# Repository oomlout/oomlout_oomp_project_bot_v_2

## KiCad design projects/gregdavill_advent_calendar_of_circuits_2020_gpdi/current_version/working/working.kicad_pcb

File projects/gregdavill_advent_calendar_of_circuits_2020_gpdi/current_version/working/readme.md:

# advent_calendar_of_circuits_2020
 
## summary 
* id: gregdavill_advent_calendar_of_circuits_2020_gpdi
* user: gregdavill
* name: advent_calendar_of_circuits_2020
* board: gpdi
* repo: https://github.com/gregdavill/advent-calendar-of-circuits-2020
* src_file_repo_kicad_pcb: gpdi/kicad-src/gpdi.kicad_pcb
* src_file_repo_kicad_pcb_link: https://github.com/gregdavill/advent-calendar-of-circuits-2020/tree/main/gpdi/kicad-src/gpdi.kicad_pcb
* src_file_repo_kicad_sch: gpdi/kicad-src/gpdi-sink.kicad_sch
* src_file_repo_kicad_sch_link: https://github.com/gregdavill/advent-calendar-of-circuits-2020/tree/main/gpdi/kicad-src/gpdi-sink.kicad_sch

* src_file_repo_sch: 
* src_file_repo_sch_link: https://github.com/gregdavill/advent-calendar-of-circuits-2020/tree/main/
* full details link: https://github.com/oomlout/oomlout_oomp_project_bot_v_2/tree/main/projects/gregdavill_advent_calendar_of_circuits_2020_gpdi/current_version/working

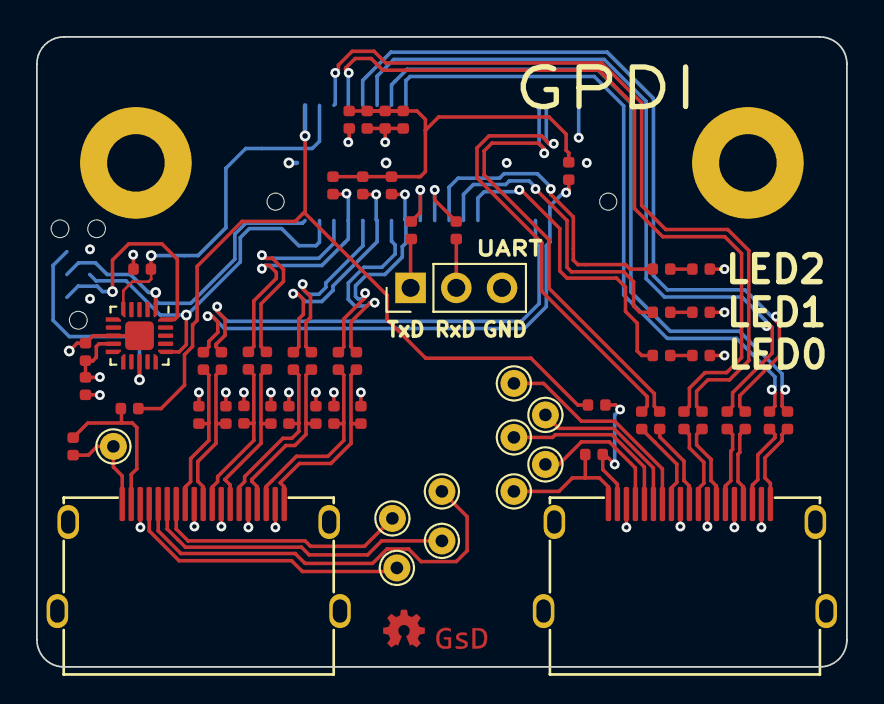
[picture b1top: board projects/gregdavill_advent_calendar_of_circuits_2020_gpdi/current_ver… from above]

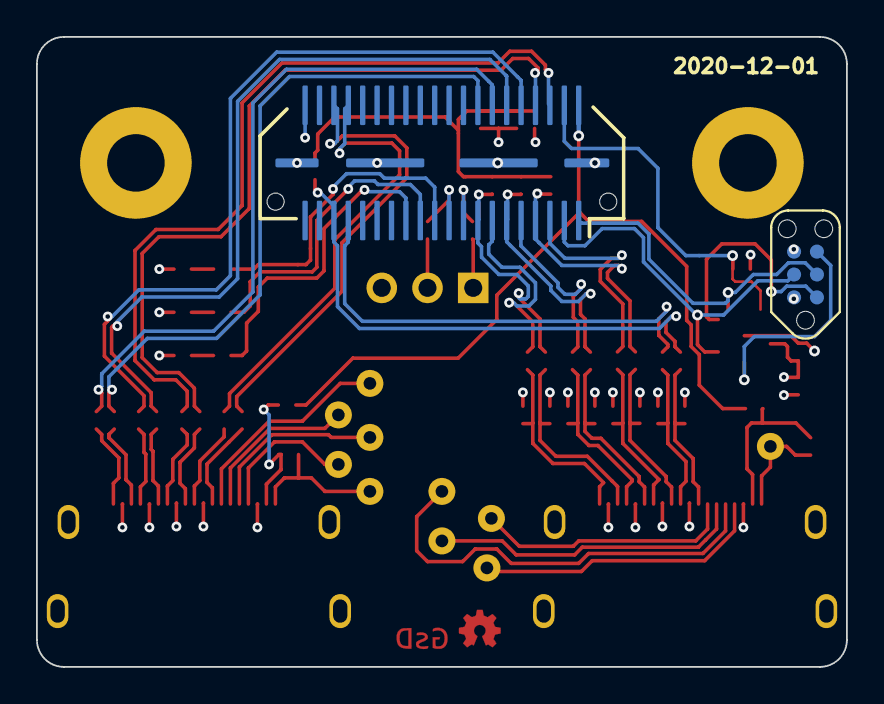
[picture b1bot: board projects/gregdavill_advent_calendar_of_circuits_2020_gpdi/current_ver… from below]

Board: 4 copper layers, 45.0 x 35.0 mm, 63 parts (2 on the bottom side), 63 nets.

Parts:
C1, C2, C3, C4, C5, C6, C7, C8, C9, C11, C13, C14, C15, C16, C17, C18, C19, C20: 0.1uF; C_0402_1005Metric
C10: 1uF; C_0402_1005Metric
C12: 4.7uF; C_0402_1005Metric
D2, D3, D4: LED_ALT; LED_0402_1005Metric
J1: SYZYGY-STD; SYZYGY-STD-POD
J2, J5: GPDI_A_1.4; HDMI-10029449-111RLF
J3: TagConnect; TC2030-NL_SMALL
J4: Conn_01x03_Male; PinHeader_1x03_P2.54mm_Vertical
R1, R3, R6, R9, R11, R12, R16, R17: 1k; R_0402_1005Metric
R2: 2k; R_0402_1005Metric
R4, R5, R7, R8: 47k; R_0402_1005Metric
R10, R13, R14, R18, R19, R20, R21, R22: 50R; R_0402_1005Metric
R15: 10K; R_0402_1005Metric
R23: 0R; R_0402_1005Metric
R24: DNP; R_0402_1005Metric
TP1, TP2, TP3, TP4, TP5, TP6, TP7, TP8, TP9, TP10: TestPoint; TestPoint_THTPad_D1.5mm_Drill0.7mm
U2: ATtiny44A-MMH; QFN-20-1EP_3x3mm_P0.45mm_EP1.6x1.6mm

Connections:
+3V3: C9.1, C10.1, J1.40 (+3.3V), J3.2, R2.1, R10.1, R13.1, R14.1, R15.1, R18.1, R19.1, R20.1, R21.1, R22.1, U2.9 (VCC)
+5V: J1.2 (+5V), R23.1, R24.1
/GPDI0.CK_N: C4.1, J1.36 (C2P_CLKN)
/GPDI0.CK_P: C8.1, J1.34 (C2P_CLKP)
/GPDI0.D0_N: C3.1, J1.8 (S3_D1N)
/GPDI0.D0_P: C7.1, J1.6 (S1_D1P)
/GPDI0.D1_N: C2.1, J1.12 (S7_D3N)
/GPDI0.D1_P: C6.1, J1.10 (S5_D3P)
/GPDI0.D2_N: C1.1, J1.16 (S11_D5N)
/GPDI0.D2_P: C5.1, J1.14 (S9_D5P)
/GPDI1.CK_N: C16.1, J1.35 (P2C_CLKN), R8.2
/GPDI1.CK_P: C20.1, J1.33 (P2C_CLKP)
/GPDI1.D0_N: C15.1, J1.7 (S2_D0N), R7.2
/GPDI1.D0_P: C19.1, J1.5 (S0_D0P)
/GPDI1.D1_N: C14.1, J1.11 (S6_D2N), R5.2
/GPDI1.D1_P: C18.1, J1.9 (S4_D2P)
/GPDI1.D2_N: C13.1, J1.15 (S10_D4N), R4.2
/GPDI1.D2_P: C17.1, J1.13 (S8_D4P)
/LED0: J1.25 (S20), R6.1
/LED1: J1.23 (S18), R11.1
/LED2: J1.21 (S16), R12.1
/Peripheral MCU/MISO: J3.1, U2.20 (PA5)
/Peripheral MCU/~RESET: J3.5, U2.13 (~RESET~/PB3)
/RGA: J1.4 (R_GA), R15.2, U2.5 (AREF/PA0)
/RxD: J1.19 (S14_D6N), R17.2
/SCL: J1.1 (SCL), J3.3, U2.1 (PA4)
/SDA: J1.3 (SDA), J3.4, U2.16 (PA6)
/TxD: J1.17 (S12_D6P), R16.2
/gpdi-0/_CK_N: C4.2, J2.12 (CK-)
/gpdi-0/_CK_P: C8.2, J2.10 (CK+)
/gpdi-0/_D0_N: C3.2, J2.9 (D0-)
/gpdi-0/_D0_P: C7.2, J2.7 (D0+)
/gpdi-0/_D1_N: C2.2, J2.6 (D1-)
/gpdi-0/_D1_P: C6.2, J2.4 (D1+)
/gpdi-0/_D2_N: C1.2, J2.3 (D2-)
/gpdi-0/_D2_P: C5.2, J2.1 (D2+)
/gpdi-1/_CK_N: C16.2, J5.12 (CK-), R10.2
/gpdi-1/_CK_P: C20.2, J5.10 (CK+), R13.2
/gpdi-1/_D0_N: C15.2, J5.9 (D0-), R14.2
/gpdi-1/_D0_P: C19.2, J5.7 (D0+), R18.2
/gpdi-1/_D1_N: C14.2, J5.6 (D1-), R19.2
/gpdi-1/_D1_P: C18.2, J5.4 (D1+), R20.2
/gpdi-1/_D2_N: C13.2, J5.3 (D2-), R21.2
/gpdi-1/_D2_P: C17.2, J5.1 (D2+), R22.2
GND: C9.2, C10.2, C11.2, C12.2, D2.1 (K), D3.1 (K), D4.1 (K), J1.41 (GND), J2.2 (D2S), J2.5 (D1S), J2.8 (D0S), J2.11 (CKS), J2.17 (GND), J2.SH, J3.6, J4.3, J5.2 (D2S), J5.5 (D1S), J5.8 (D0S), J5.11 (CKS), J5.17 (GND), J5.SH, R3.2, U2.8 (GND), U2.21 (GND)
unnamed: C11.1, C12.1, R2.2, R3.1, R4.1, R5.1, R7.1, R8.1
unnamed: D2.2 (A), R6.2
unnamed: D3.2 (A), R11.2
unnamed: D4.2 (A), R12.2
unnamed: J2.13 (CEC), TP2.1
unnamed: J2.14 (UTILITY/HEAC+), TP5.1
unnamed: J2.15 (SCL), TP3.1
unnamed: J2.16 (SDA), TP4.1
unnamed: J2.18 (+5V), R1.1, R23.2
unnamed: J2.19 (HPD/HEAC-), R1.2, TP1.1
unnamed: J4.1, R16.1
unnamed: J4.2, R17.1
unnamed: J5.13 (CEC), TP7.1
unnamed: J5.14 (UTILITY/HEAC+), TP10.1
unnamed: J5.15 (SCL), TP8.1
unnamed: J5.16 (SDA), TP9.1
unnamed: J5.18 (+5V), R9.1, R24.2
unnamed: J5.19 (HPD/HEAC-), R9.2, TP6.1

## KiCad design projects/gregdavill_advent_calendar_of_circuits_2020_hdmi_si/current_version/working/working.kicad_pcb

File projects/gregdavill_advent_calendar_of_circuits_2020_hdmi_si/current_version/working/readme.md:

# advent_calendar_of_circuits_2020
 
## summary 
* id: gregdavill_advent_calendar_of_circuits_2020_hdmi_si
* user: gregdavill
* name: advent_calendar_of_circuits_2020
* board: hdmi_si
* repo: https://github.com/gregdavill/advent-calendar-of-circuits-2020
* src_file_repo_kicad_pcb: hdmi-si/kicad-src/hdmi-si.kicad_pcb
* src_file_repo_kicad_pcb_link: https://github.com/gregdavill/advent-calendar-of-circuits-2020/tree/main/hdmi-si/kicad-src/hdmi-si.kicad_pcb
* src_file_repo_kicad_sch: hdmi-si/kicad-src/hdmi-si.kicad_sch
* src_file_repo_kicad_sch_link: https://github.com/gregdavill/advent-calendar-of-circuits-2020/tree/main/hdmi-si/kicad-src/hdmi-si.kicad_sch

* src_file_repo_sch: 
* src_file_repo_sch_link: https://github.com/gregdavill/advent-calendar-of-circuits-2020/tree/main/
* full details link: https://github.com/oomlout/oomlout_oomp_project_bot_v_2/tree/main/projects/gregdavill_advent_calendar_of_circuits_2020_hdmi_si/current_version/working

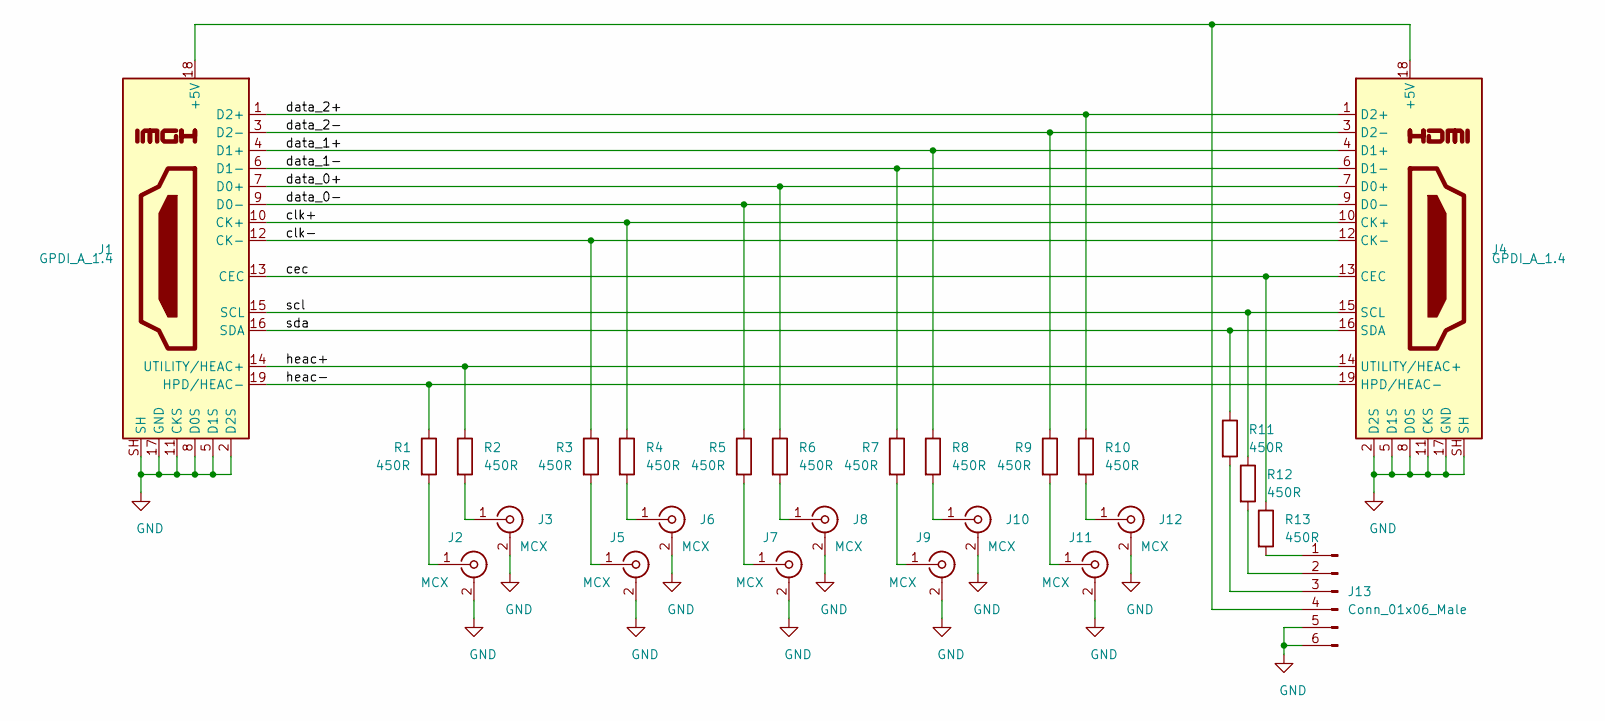
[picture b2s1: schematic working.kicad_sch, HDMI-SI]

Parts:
J1, J4: GPDI_A_1.4; HDMI-10029449-111RLF
J2, J3, J5, J6, J7, J8, J9, J10, J11, J12: MCX; MMCX_Molex_73415-1471_Vertical
J13: Conn_01x06_Male; PinHeader_1x06_P2.54mm_Vertical
R1, R2, R3, R4, R5, R6, R7, R8, R9, R10, R11, R12, R13: 450R; R_0402_1005Metric

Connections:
/cec: J1.13 (CEC), J4.13 (CEC), R13.1
/clk+: J1.10 (CK+), J4.10 (CK+), R4.1
/clk-: J1.12 (CK-), J4.12 (CK-), R3.1
/data_0+: J1.7 (D0+), J4.7 (D0+), R6.1
/data_0-: J1.9 (D0-), J4.9 (D0-), R5.1
/data_1+: J1.4 (D1+), J4.4 (D1+), R8.1
/data_1-: J1.6 (D1-), J4.6 (D1-), R7.1
/data_2+: J1.1 (D2+), J4.1 (D2+), R10.1
/data_2-: J1.3 (D2-), J4.3 (D2-), R9.1
/heac+: J1.14 (UTILITY/HEAC+), J4.14 (UTILITY/HEAC+), R2.1
/heac-: J1.19 (HPD/HEAC-), J4.19 (HPD/HEAC-), R1.1
/scl: J1.15 (SCL), J4.15 (SCL), R12.1
/sda: J1.16 (SDA), J4.16 (SDA), R11.1
GND: J1.2 (D2S), J1.5 (D1S), J1.8 (D0S), J1.11 (CKS), J1.17 (GND), J1.SH, J2.2 (Ext), J3.2 (Ext), J4.2 (D2S), J4.5 (D1S), J4.8 (D0S), J4.11 (CKS), J4.17 (GND), J4.SH, J5.2 (Ext), J6.2 (Ext), J7.2 (Ext), J8.2 (Ext), J9.2 (Ext), J10.2 (Ext), J11.2 (Ext), J12.2 (Ext), J13.5, J13.6
unnamed: J1.18 (+5V), J4.18 (+5V), J13.4
unnamed: J2.1 (In), R1.2
unnamed: J3.1 (In), R2.2
unnamed: J5.1 (In), R3.2
unnamed: J6.1 (In), R4.2
unnamed: J7.1 (In), R5.2
unnamed: J8.1 (In), R6.2
unnamed: J9.1 (In), R7.2
unnamed: J10.1 (In), R8.2
unnamed: J11.1 (In), R9.2
unnamed: J12.1 (In), R10.2
unnamed: J13.1, R13.2
unnamed: J13.2, R12.2
unnamed: J13.3, R11.2

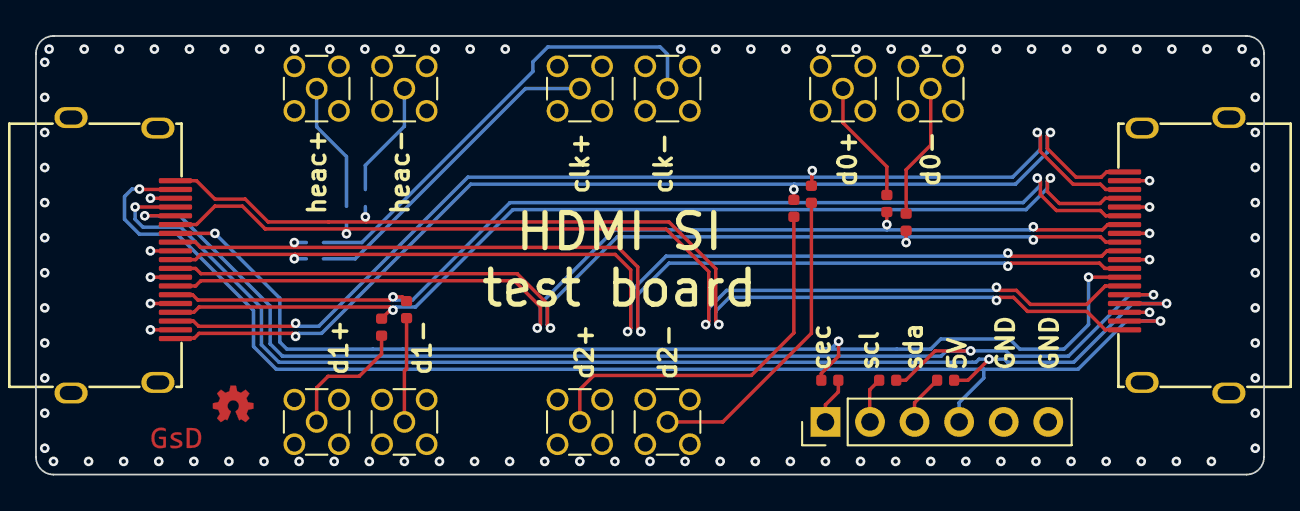
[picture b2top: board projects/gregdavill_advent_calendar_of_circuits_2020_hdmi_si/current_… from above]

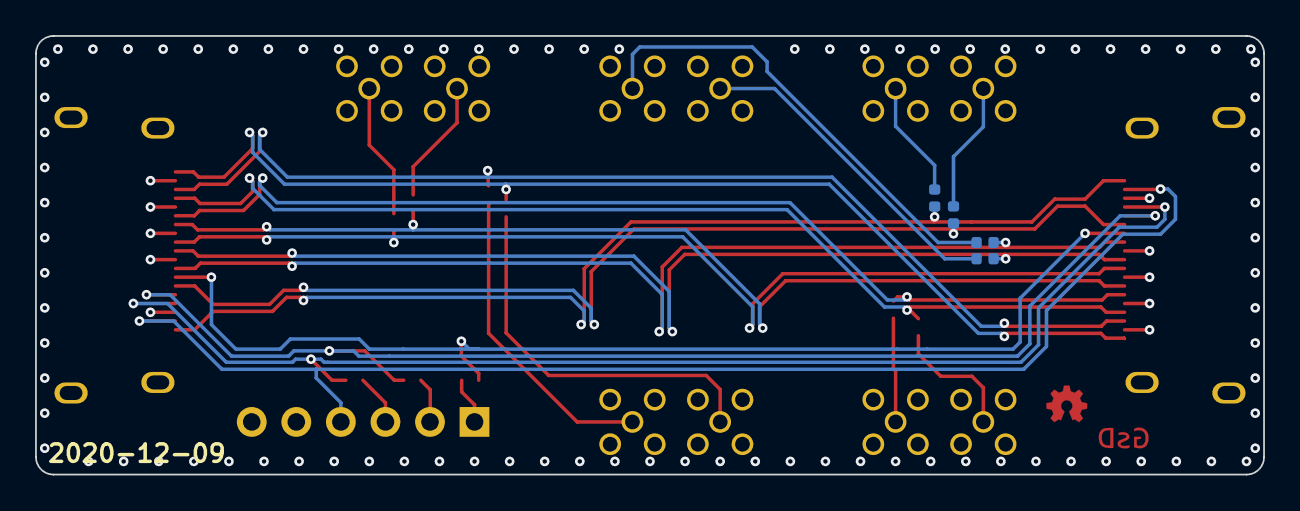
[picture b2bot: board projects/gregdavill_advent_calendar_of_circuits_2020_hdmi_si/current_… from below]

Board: 4 copper layers, 70.0 x 25.0 mm, 26 parts (4 on the bottom side), 28 nets.

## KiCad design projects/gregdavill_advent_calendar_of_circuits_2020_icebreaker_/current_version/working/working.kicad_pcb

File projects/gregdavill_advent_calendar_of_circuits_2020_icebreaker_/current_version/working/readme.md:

# advent_calendar_of_circuits_2020
 
## summary 
* id: gregdavill_advent_calendar_of_circuits_2020_icebreaker_
* user: gregdavill
* name: advent_calendar_of_circuits_2020
* board: icebreaker_
* repo: https://github.com/gregdavill/advent-calendar-of-circuits-2020
* src_file_repo_kicad_pcb: icebreaker++-ram/kicad-src/icebreaker++.kicad_pcb
* src_file_repo_kicad_pcb_link: https://github.com/gregdavill/advent-calendar-of-circuits-2020/tree/main/icebreaker++-ram/kicad-src/icebreaker++.kicad_pcb
* src_file_repo_kicad_sch: icebreaker++-ram/kicad-src/fpga.kicad_sch
* src_file_repo_kicad_sch_link: https://github.com/gregdavill/advent-calendar-of-circuits-2020/tree/main/icebreaker++-ram/kicad-src/fpga.kicad_sch

* src_file_repo_sch: 
* src_file_repo_sch_link: https://github.com/gregdavill/advent-calendar-of-circuits-2020/tree/main/
* full details link: https://github.com/oomlout/oomlout_oomp_project_bot_v_2/tree/main/projects/gregdavill_advent_calendar_of_circuits_2020_icebreaker_/current_version/working

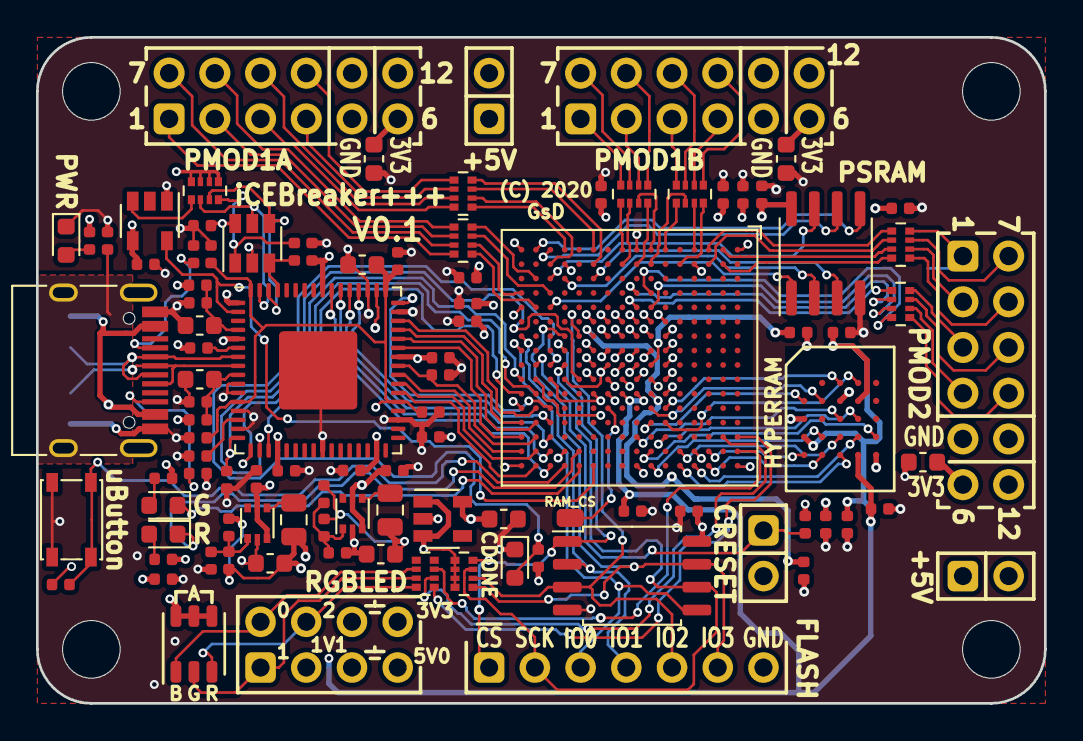
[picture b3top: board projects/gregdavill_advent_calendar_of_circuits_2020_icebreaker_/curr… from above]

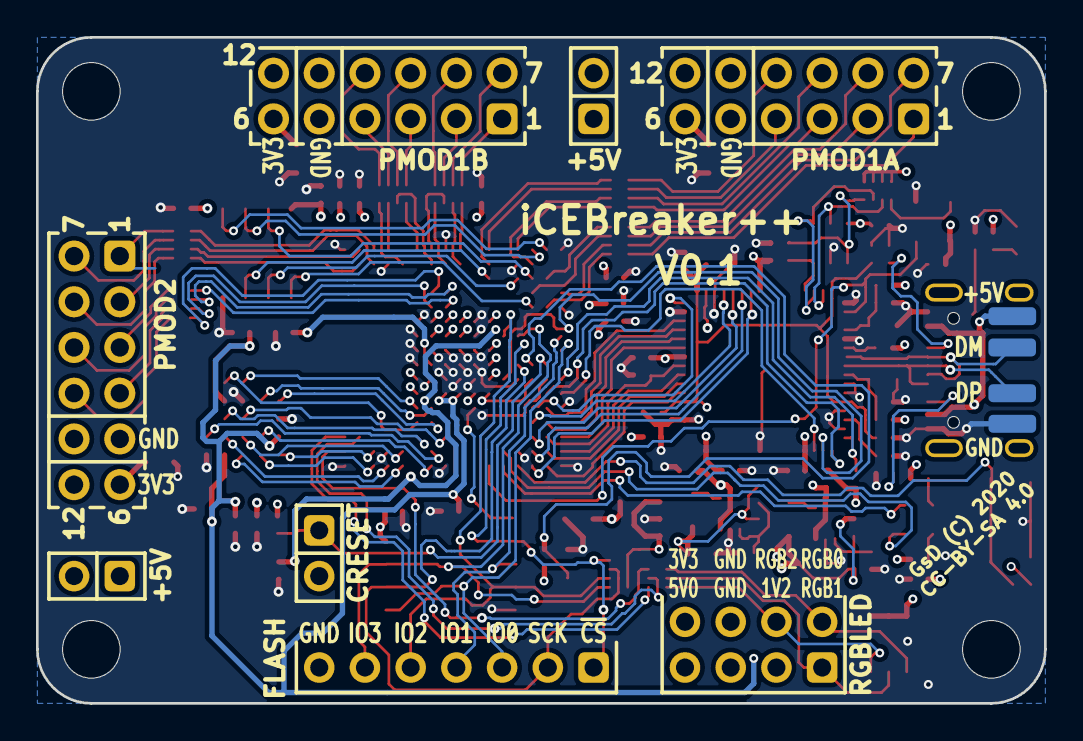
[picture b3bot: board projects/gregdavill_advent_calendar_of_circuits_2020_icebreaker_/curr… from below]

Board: 4 copper layers, 56.0 x 37.0 mm, 104 parts (4 on the bottom side), 130 nets.

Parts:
C1, C4, C10, C12, C13, C14, C16, C17, C18, C19, C20, C21, C22: 100n; C_0402_1005Metric
C2, C3, C5, C8, C11, C35, C36, C37, C38, C39, C40, C41, C42, C43: 0.1uF; C_0402_1005Metric
C6, C7, C9: 4u7; C_0603_1608Metric
C15, C23: 4.7uF; C_0402_1005Metric
C24, C28, C29: 10uF; C_0603_1608Metric
C25, C30, C31: 1uF; C_0402_1005Metric
C26, C27: 6.8pF; C_0402_1005Metric
C32, C33, C34: DNP; C_0603_1608Metric
D1, D4: GRN; LED_0603_1608Metric
D3: BLU; LED_0603_1608Metric
D5: RED; LED_0603_1608Metric
D11: LED_RGB; LED_Cree_PLCC6_3.4x3.4mm
J20: Flash; PinHeader_1x07_P2.54mm_Vertical
J21, J23, J27: PMOD; PMOD_Angled_2x06
J22, J26: 5V AUX; PinHeader_2x01_P2.54mm_Vertical
J24: USB_C_Receptacle_USB2.0; USB_C_Receptacle_HRO_TYPE-C-31-M-12
J25: RGB Led; PinHeader_2x04_P2.54mm_Vertical
J28: CRESET; PinHeader_2x01_P2.54mm_Vertical
L1, L2: 600; L_0402_1005Metric
L3, L4: 2.2uH; L_0805_2012Metric
P2, P3, P4, P5: UP; PAD_SMD_1x2.65
P6: RAM_CS; PAD_SMD_1x1.5
R1: 1M; R_0402_1005Metric
R2, R11: 10k; R_Array_Convex_4x0402
R3, R4, R7, R16, R17, R18, R27: 33R; R_Array_Convex_4x0402
R5, R14, R15: 330E; R_0402_1005Metric
R6, R12: 2k2; R_0402_1005Metric
R8: 12k; R_0402_1005Metric
R9, R13, R19, R25: 10k; R_0402_1005Metric
R10: 210k; R_0402_1005Metric
R20: 1k; R_0402_1005Metric
R21, R22: 5.1k; R_0402_1005Metric
R23: 47k; R_0402_1005Metric
R24: 84k5; R_0402_1005Metric
R26: 100k; R_0402_1005Metric
SW1: TACT; SW_SPST_PTS810
U1: 93C46B-SOT-23-6; SOT-23-6
U2: FT2232H; QFN-64-1EP_9x9mm_P0.5mm_EP4.35x4.35mm
U3: W25Q32JVSS; SOIC-8_5.23x5.23mm_P1.27mm
U4, U5: TLV62569DRL; SOT-666
U6: TLV713285PDBV; SOT-23-5
U7: 12MHz; SOT-23-5
U8: ECP5U-12-CABGA256; BGA-256_14.0x14.0mm_Layout16x16_P0.8mm_Ball0.45mm_Pad0.32mm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
U9: LY68L6400SLIT; SOIC-8_3.9x4.9mm_P1.27mm
U10: IS66WVH16M8ALL; BGA-24_8.0x6.0mm_Layout5x5_P0.8mm_Pad0.35mm_NSMD

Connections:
+1V1: C27.1, C29.1, C31.1, C35.1, C36.1, C37.1, C38.1, L4.2, R24.2, U8.G6 (VCC[6]), U8.G7 (VCC[6]), U8.G9 (VCC[6]), U8.L8 (VCC[6]), U8.L9 (VCC[6]), U8.L10 (VCC[6])
+1V8: C7.1, C8.1, C10.1, C14.1, C16.1, C17.1, C40.1, C41.1, C42.1, U2.12 (VCORE), U2.37 (VCORE), U2.49 (VREGOUT), U2.64 (VCORE), U8.H11 (VCCIO2[2]), U8.J11 (VCCIO2[2]), U10.B4 (VCC), U10.D1 (VCCQ), U10.E4 (VCCQ)
+2V5: C24.1, C25.1, U6.5 (OUT), U8.G11 (VCCAUX[2]), U8.L7 (VCCAUX[2])
+3V3: C1.1, C2.1, C3.1, C4.1, C5.1, C11.1, C18.1, C19.1, C20.1, C21.1, C22.1, C26.1, C28.1, C30.1, C32.2, C33.2, C34.2, C39.1, C43.1, D11.4 (BA), D11.5 (GA), D11.6 (RA), J21.6, J21.12, J23.6, J23.12, J25.8, J27.6, J27.12, L1.1, L2.1, L3.2, R2.5, R2.6, R2.7, R2.8, R5.1, R9.2, R10.2, R11.1, R11.2, R11.3, R11.4, R12.1, R13.2, R14.2, R15.2, R19.1, U1.6 (VCC), U2.20 (VCCIO), U2.31 (VCCIO), U2.42 (VCCIO), U2.50 (VREGIN), U2.56 (VCCIO), U3.8 (VCC), U6.1 (IN), U6.3 (EN), U7.4 (VDD), U8.F10 (VCCIO1[2]), U8.F11 (VCCIO1[2]), U8.H6 (VCCIO7[2]), U8.H7 (VCCIO7[2]), U8.J6 (VCCIO6[2]), U8.J7 (VCCIO6[2]), U8.K11 (VCCIO3[2]), U8.L6 (VCCIO8), U8.L11 (VCCIO3[2]), U8.P10 (CFG_1), U9.8 (VCC)
+5V: C15.1, C23.1, J22.1, J24.A4 (VBUS), J24.A9 (VBUS), J24.B4 (VBUS), J24.B9 (VBUS), J25.7, J26.1, P2.1 (PAD), U4.3 (VIN), U4.5 (EN), U5.3 (VIN), U5.5 (EN)
/DONE: D3.2 (A), R12.2, U8.P9 (DONE)
/FLASH_CS: J20.1, R11.8, U3.1 (~CS), U8.N8 (PB15A/+/HOLDN/DI/BUSY/CSSPIN/CEN)
/FLASH_MISO|IO1: J20.4, U3.2 (DO(IO1)), U8.T7 (PB11A/+/D1/MISO/IO1)
/FLASH_MOSI|IO0: J20.3, U3.5 (DI(IO0)), U8.T8 (PB11B/-/D0/MOSI/IO0)
/FLASH_SCK: J20.2, R11.7, U3.6 (CLK), U8.N9 (CCLK/MCLK/SCK)
/FLASH_~HLD|~RST|IO3: J20.6, R11.5, U3.7 (IO3), U8.N7 (PB9A/+/D3/IO3)
/FLASH_~WP|IO2: J20.5, R11.6, U3.3 (IO2), U8.M7 (PB9B/-/D2/IO2)
/FTDI_CLK: U2.2 (OSCI), U7.5 (OUT), U8.L16 (PR26A/+/PCLKT3_1/HS/RDQ32)
/JTAG_TCK: R20.1, U2.16 (ADBUS0), U8.T10 (TCK)
/JTAG_TDI: U2.17 (ADBUS1), U8.R11 (TDI)
/JTAG_TDO: U2.18 (ADBUS2), U8.M10 (TDO)
/JTAG_TMS: U2.19 (ADBUS3), U8.T11 (TMS)
/PMODS/P1A1: R16.5, U8.R5 (PL44A/+/HS/LDQS44)
/PMODS/P1A1x: J23.1, R16.4
/PMODS/P1A2: R16.7, U8.P4 (PL41A/+/HS/LDQ44)
/PMODS/P1A2x: J23.2, R16.2
/PMODS/P1A3: R3.5, U8.N1 (PL32A/+/HS/LDQS32)
/PMODS/P1A3x: J23.3, R3.4
/PMODS/P1A4: R3.7, U8.L1 (PL26A/+/PCLKT6_1/HS/LDQ32)
/PMODS/P1A4x: J23.4, R3.2
/PMODS/P1A7: R16.6, U8.T4 (PL44B/-/HS/LDQSN44)
/PMODS/P1A7x: J23.7, R16.3
/PMODS/P1A8: R16.8, U8.R3 (PL41B/-/HS/LDQ44)
/PMODS/P1A8x: J23.8, R16.1
/PMODS/P1A9: R3.6, U8.P2 (PL32B/-/HS/LDQSN32)
/PMODS/P1A9x: J23.9, R3.3
/PMODS/P1A10: R3.8, U8.L2 (PL26B/-/PCLKC6_1/HS/LDQ32)
/PMODS/P1A10x: J23.10, R3.1
/PMODS/P1B1: R4.1, U8.J1 (PL23A/+/PCLKT7_1/HS/LDQ20)
/PMODS/P1B1x: J27.1, R4.8
/PMODS/P1B2: R4.3, U8.G1 (PL20A/+/GR_PCLK7_1/HS/LDQS20)
/PMODS/P1B2x: J27.2, R4.6
/PMODS/P1B3: R17.1, U8.F1 (PL14A/+/HS/LDQ20)
/PMODS/P1B3x: J27.3, R17.8
/PMODS/P1B4: R17.3, U8.D1 (PL8A/+/HS/LDQS8)
/PMODS/P1B4x: J27.4, R17.6
/PMODS/P1B7: R4.2, U8.J2 (PL23B/-/PCLKC7_1/HS/LDQ20)
/PMODS/P1B7x: J27.7, R4.7
/PMODS/P1B8: R4.4, U8.H2 (PL20B/-/HS/LDQSN20)
/PMODS/P1B8x: J27.8, R4.5
/PMODS/P1B9: R17.2, U8.G2 (PL14B/-/HS/LDQ20)
/PMODS/P1B9x: J27.9, R17.7
/PMODS/P1B10: R17.4, U8.E2 (PL8B/-/HS/LDQSN8)
/PMODS/P1B10x: J27.10, R17.5
/PMODS/P2_1: R7.1, U8.C1 (PL5A/+/HS/LDQ8)
/PMODS/P2_1x: J21.1, R7.8
/PMODS/P2_2: R7.3, U8.B1 (PL2A/+/HS/LDQ8)
/PMODS/P2_2x: J21.2, R7.6
/PMODS/P2_3: R18.1, U8.H5 (PL17A/+/HS/LDQ20)
/PMODS/P2_3x: J21.3, R18.8
/PMODS/P2_4: R18.3, U8.G5 (PL11A/+/HS/LDQ8)
/PMODS/P2_4x: J21.4, R18.6
/PMODS/P2_7: R7.2, U8.C2 (PL5B/-/HS/LDQ8)
/PMODS/P2_7x: J21.7, R7.7
/PMODS/P2_8: R7.4, U8.B2 (PL2B/-/HS/LDQ8)
/PMODS/P2_8x: J21.8, R7.5
/PMODS/P2_9: R18.2, U8.H4 (PL17B/-/HS/LDQ20)
/PMODS/P2_9x: J21.9, R18.7
/PMODS/P2_10: R18.4, U8.G4 (PL11B/-/HS/LDQ8)
/PMODS/P2_10x: J21.10, R18.5
/PMODS/RAM_CLK: U8.P1 (PL35A/+/HS/LDQ32), U9.6 (CLK)
/PMODS/RAM_CS: U8.P5 (PL47D/-/LLC_GPLL0C_IN/LDQ44), U9.1 (~CS)
/PMODS/RAM_IO0: U8.R1 (PL35B/-/VREF1_6/HS/LDQ32), U9.5 (DI(IO0))
/PMODS/RAM_IO1: U8.N3 (PL35D/-/LDQ32), U9.2 (DO(IO1))
/PMODS/RAM_IO2: U8.L3 (PL32C/+/LDQ32), U9.3 (IO2)
/PMODS/RAM_IO3: U8.P3 (PL38B/-/HS/LDQ44), U9.7 (IO3)
/PROGRAMn: J28.1, R19.2, U8.R9 (PROGRAMN)
/RAM/HRAM_CLK: U8.G12 (PR11A/+/HS/RDQ8), U10.B2 (CK)
/RAM/HRAM_CLK#: U8.G13 (PR11B/-/HS/RDQ8), U10.B1 (CK#)
/RAM/HRAM_CS: U8.F12 (PR8D/-/RDQ8), U10.A3 (CS#)
/RAM/HRAM_DQ0: U8.E15 (PR8B/-/HS/RDQSN8), U10.D3 (DQ0)
/RAM/HRAM_DQ1: U8.G16 (PR20A/+/GR_PCLK2_1/HS/RDQS20), U10.D2 (DQ1)
/RAM/HRAM_DQ2: U8.F14 (PR5D/-/RDQ8), U10.C4 (DQ2)
/RAM/HRAM_DQ3: U8.D16 (PR8A/+/HS/RDQS8), U10.D4 (DQ3)
/RAM/HRAM_DQ4: U8.G15 (PR14B/-/HS/RDQ20), U10.D5 (DQ4)
/RAM/HRAM_DQ5: U8.E16 (PR11D/-/RDQ8), U10.E3 (DQ5)
/RAM/HRAM_DQ6: U8.C16 (PR5A/+/HS/RDQ8), U10.E2 (DQ6)
/RAM/HRAM_DQ7: U8.C15 (PR5B/-/HS/RDQ8), U10.E1 (DQ7)
/RAM/HRAM_RST: U8.F13 (PR8C/+/RDQ8), U10.A4 (RESET#)
/RAM/HRAM_RWDS: U8.H14 (PR14D/-/RDQ20), U10.C3 (RWDS)
/RAM_CS: P6.1 (PAD), U8.K12 (PR29B/-/HS/RDQ32)
/USB_DM: J24.A7 (D-), J24.B7 (D-), P3.1 (PAD), U2.7 (DM)
/USB_DP: J24.A6 (D+), J24.B6 (D+), P4.1 (PAD), U2.8 (DP)
/shield: J24.S1 (SHIELD), R1.2
/xFIFO_D0: U2.38 (BDBUS0), U8.R16 (PR35B/-/VREF1_3/HS/RDQ32)
/xFIFO_D1: U2.39 (BDBUS1), U8.R15 (PR38C/+/RDQ44)
/xFIFO_D2: U2.40 (BDBUS2), U8.T15 (PR38D/-/RDQ44)
/xFIFO_D3: R25.1, U2.41 (BDBUS3), U8.R14 (PR41B/-/HS/RDQ44)
/xFIFO_D4: U2.43 (BDBUS4), U8.T14 (PR41D/-/RDQ44)
/xFIFO_D5: U2.44 (BDBUS5), U8.R13 (PR41C/+/RDQ44)
/xFIFO_D6: U2.45 (BDBUS6), U8.T13 (PR44B/-/HS/RDQSN44)
/xFIFO_D7: U2.46 (BDBUS7), U8.R12 (PR44A/+/HS/RDQS44)
/xFIFO_WKUP: U2.55 (BCBUS4), U8.P16 (PR35A/+/HS/RDQ32)
/xFIFO_~RD: U2.53 (BCBUS2), U8.P14 (PR38B/-/HS/RDQ44)
/xFIFO_~RXF: U2.48 (BCBUS0), U8.P12 (PR47D/-/LRC_GPLL0C_IN/RDQ44)
/xFIFO_~TXE: U2.52 (BCBUS1), U8.P13 (PR41A/+/HS/RDQ44)
/xFIFO_~WR: U2.54 (BCBUS3), U8.P15 (PR32B/-/HS/RDQSN32)
/~BUTTON: R13.1, SW1.1, U8.N16 (PR32A/+/HS/RDQS32)
/~LEDG: D4.1 (K), U8.M16 (PR26C/+/PCLKT3_0/RDQ32)
/~LEDR: D5.1 (K), U8.M15 (PR26D/-/PCLKC3_0/RDQ32)
/~LED_RGB0: D11.1 (RK), J25.2, R27.2
/~LED_RGB1: D11.2 (GK), J25.1, R27.3
/~LED_RGB2: D11.3 (BK), J25.4, R27.4
GND: C1.2, C2.2, C3.2, C4.2, C5.2, C6.2, C7.2, C8.2, C9.2, C10.2, C11.2, C12.2, C13.2, C14.2, C15.2, C16.2, C17.2, C18.2, C19.2, C20.2, C21.2, C22.2, C23.2, C24.2, C25.2, C28.2, C29.2, C30.2, C31.2, C32.1, C33.1, C34.1, C35.2, C36.2, C37.2, C38.2, C39.2, C40.2, C41.2, C42.2, C43.2, D1.1 (K), D3.1 (K), J20.7, J21.5, J21.11, J22.2, J23.5, J23.11, J24.A1 (GND), J24.A12 (GND), J24.B1 (GND), J24.B12 (GND), J25.5, J25.6, J26.2, J27.5, J27.11, J28.2, P5.1 (PAD), R1.1, R8.2, R20.2, R21.1, R22.1, R23.1, R25.2, R26.1, SW1.2, U1.2 (VSS), U2.1 (GND), U2.5 (GND), U2.10 (AGND), U2.11 (GND), U2.13 (TEST), U2.15 (GND), U2.25 (GND), U2.35 (GND), U2.47 (GND), U2.51 (GND), U3.4 (GND), U4.2 (GND), U5.2 (GND), U6.2 (GND), U7.1 (GND), U8.A1 (GND[27]), U8.A16 (GND[27]), U8.D2 (GND[27]), U8.D15 (GND[27]), U8.F6 (VCCIO0[2]), U8.F7 (VCCIO0[2]), U8.F8 (GND[27]), U8.F9 (GND[27]), U8.G8 (GND[27]), U8.G10 (GND[27]), U8.H1 (GND[27]), U8.H8 (GND[27]), U8.H9 (GND[27]), U8.H10 (GND[27]), U8.H16 (GND[27]), U8.J8 (GND[27]), U8.J9 (GND[27]), U8.J10 (GND[27]), U8.K6 (GND[27]), U8.K7 (GND[27]), U8.K8 (GND[27]), U8.K9 (GND[27]), U8.K10 (GND[27]), U8.N2 (GND[27]), U8.N10 (CFG_0), U8.N15 (GND[27]), U8.R10 (CFG_2), U8.T1 (GND[27]), U8.T5 (GND[27]), U8.T12 (GND[27]), U8.T16 (GND[27]), U9.4 (GND), U10.B3 (VSS), U10.C1 (VSSQ), U10.E5 (VSSQ)
unnamed: C6.1, C12.1, L2.2, U2.4 (VPHY)
unnamed: C9.1, C13.1, L1.2, U2.9 (VPLL)
unnamed: C26.2, R10.1, R23.2, U4.1 (FB)
unnamed: C27.2, R24.1, R26.2, U5.1 (FB)
unnamed: D1.2 (A), R5.2
unnamed: D4.2 (A), R14.1
unnamed: D5.2 (A), R15.1
unnamed: J24.A5 (CC1), R21.2
unnamed: J24.B5 (CC2), R22.2
unnamed: L3.1, U4.4 (SW)
unnamed: L4.1, U5.4 (SW)
unnamed: R2.1, U7.3 (OE/~ST~/NC)
unnamed: R2.2, U1.5 (CS), U2.63 (EECS)
unnamed: R2.3, U1.4 (CLK), U2.62 (EECLK)
unnamed: R2.4, R6.2, U1.1 (DO)
unnamed: R6.1, U1.3 (DI), U2.61 (EEDATA)
unnamed: R8.1, U2.14 (~RESET)
unnamed: R9.1, U2.6 (REF)
unnamed: R27.5, U8.A14 (PT65B/-)
unnamed: R27.7, U8.A15 (PT67B/-)
unnamed: R27.6, U8.B14 (PT67A/+)

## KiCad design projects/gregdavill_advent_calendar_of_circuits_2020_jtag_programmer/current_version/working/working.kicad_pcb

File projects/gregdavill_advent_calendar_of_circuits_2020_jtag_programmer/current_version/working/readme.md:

# advent_calendar_of_circuits_2020
 
## summary 
* id: gregdavill_advent_calendar_of_circuits_2020_jtag_programmer
* user: gregdavill
* name: advent_calendar_of_circuits_2020
* board: jtag_programmer
* repo: https://github.com/gregdavill/advent-calendar-of-circuits-2020
* src_file_repo_kicad_pcb: jtag-programmer/kicad-src/jtag-programmer.kicad_pcb
* src_file_repo_kicad_pcb_link: https://github.com/gregdavill/advent-calendar-of-circuits-2020/tree/main/jtag-programmer/kicad-src/jtag-programmer.kicad_pcb
* src_file_repo_kicad_sch: jtag-programmer/kicad-src/jtag-programmer.kicad_sch
* src_file_repo_kicad_sch_link: https://github.com/gregdavill/advent-calendar-of-circuits-2020/tree/main/jtag-programmer/kicad-src/jtag-programmer.kicad_sch

* src_file_repo_sch: 
* src_file_repo_sch_link: https://github.com/gregdavill/advent-calendar-of-circuits-2020/tree/main/
* full details link: https://github.com/oomlout/oomlout_oomp_project_bot_v_2/tree/main/projects/gregdavill_advent_calendar_of_circuits_2020_jtag_programmer/current_version/working

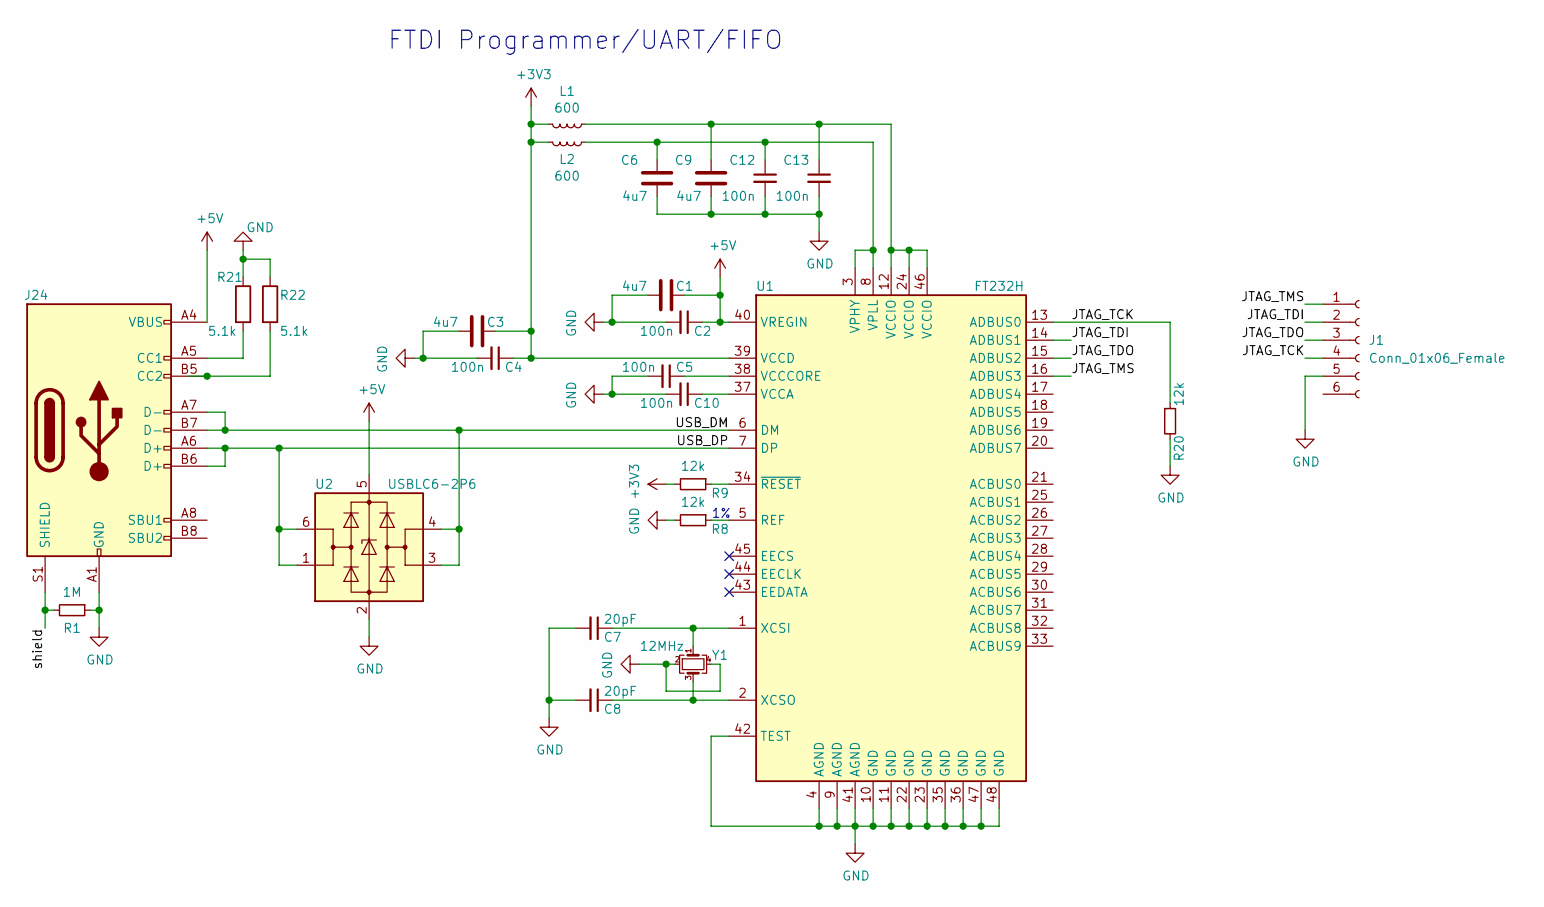
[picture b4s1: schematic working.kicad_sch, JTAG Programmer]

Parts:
C1, C3, C6, C9: 4u7; C_0603_1608Metric
C2, C4, C5, C10, C12, C13: 100n; C_0402_1005Metric
C7, C8: 20pF; C_0402_1005Metric
J1: Conn_01x06_Female; PinSocket_1x06_P2.54mm_Horizontal
J24: USB_C_Receptacle_USB2.0; USB_C_Receptacle_HRO_TYPE-C-31-M-12
L1, L2: 600; L_0402_1005Metric
R1: 1M; R_0402_1005Metric
R8, R9, R20: 12k; R_0402_1005Metric
R21, R22: 5.1k; R_0402_1005Metric
U1: FT232H; QFN-48-1EP_8x8mm_P0.5mm_EP6.2x6.2mm
U2: USBLC6-2P6; SOT-666
Y1: 12MHz; Crystal_SMD_3225-4Pin_3.2x2.5mm

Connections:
+3V3: C3.1, C4.1, L1.1, L2.1, R9.2, U1.39 (VCCD)
+5V: C1.1, C2.1, J24.A4 (VBUS), J24.A9 (VBUS), J24.B4 (VBUS), J24.B9 (VBUS), U1.40 (VREGIN), U2.5 (VBUS)
/JTAG_TCK: J1.4, R20.1, U1.13 (ADBUS0)
/JTAG_TDI: J1.2, U1.14 (ADBUS1)
/JTAG_TDO: J1.3, U1.15 (ADBUS2)
/JTAG_TMS: J1.1, U1.16 (ADBUS3)
/USB_DM: J24.A7 (D-), J24.B7 (D-), U1.6 (DM), U2.3 (I/O2), U2.4 (I/O2)
/USB_DP: J24.A6 (D+), J24.B6 (D+), U1.7 (DP), U2.1 (I/O1), U2.6 (I/O1)
/shield: J24.S1 (SHIELD), R1.2
GND: C1.2, C2.2, C3.2, C4.2, C5.2, C6.2, C7.2, C8.2, C9.2, C10.2, C12.2, C13.2, J1.5, J24.A1 (GND), J24.A12 (GND), J24.B1 (GND), J24.B12 (GND), R1.1, R8.2, R20.2, R21.1, R22.1, U1.4 (AGND), U1.9 (AGND), U1.10 (GND), U1.11 (GND), U1.22 (GND), U1.23 (GND), U1.35 (GND), U1.36 (GND), U1.41 (AGND), U1.42 (TEST), U1.47 (GND), U1.48 (GND), U1.49, U2.2 (GND), Y1.2, Y1.4
unnamed: C5.1, U1.38 (VCCCORE)
unnamed: C7.1, U1.1 (XCSI), Y1.1
unnamed: C8.1, U1.2 (XCSO), Y1.3
unnamed: C10.1, U1.37 (VCCA)
unnamed: C6.1, C12.1, L2.2, U1.3 (VPHY), U1.8 (VPLL)
unnamed: C9.1, C13.1, L1.2, U1.12 (VCCIO), U1.24 (VCCIO), U1.46 (VCCIO)
unnamed: J24.A5 (CC1), R21.2
unnamed: J24.B5 (CC2), R22.2
unnamed: R8.1, U1.5 (REF)
unnamed: R9.1, U1.34 (~RESET)
no_connect_38: U1.43 (EEDATA)
no_connect_39: U1.44 (EECLK)
no_connect_40: U1.45 (EECS)

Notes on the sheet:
FTDI Programmer/UART/FIFO

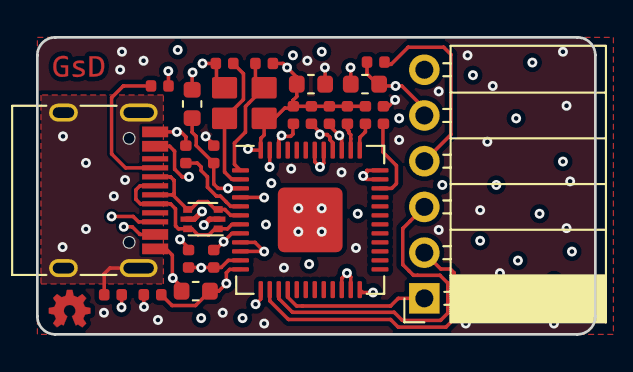
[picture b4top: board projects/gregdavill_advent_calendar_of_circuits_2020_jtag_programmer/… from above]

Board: 4 copper layers, 31.0 x 16.5 mm, 25 parts (0 on the bottom side), 20 nets.

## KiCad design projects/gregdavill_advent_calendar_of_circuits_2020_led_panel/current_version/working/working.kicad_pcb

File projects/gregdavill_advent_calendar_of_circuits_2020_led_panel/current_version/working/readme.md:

# advent_calendar_of_circuits_2020
 
## summary 
* id: gregdavill_advent_calendar_of_circuits_2020_led_panel
* user: gregdavill
* name: advent_calendar_of_circuits_2020
* board: led_panel
* repo: https://github.com/gregdavill/advent-calendar-of-circuits-2020
* src_file_repo_kicad_pcb: led-panel/kicad-src/led-panel.kicad_pcb
* src_file_repo_kicad_pcb_link: https://github.com/gregdavill/advent-calendar-of-circuits-2020/tree/main/led-panel/kicad-src/led-panel.kicad_pcb
* src_file_repo_kicad_sch: led-panel/kicad-src/led-panel.kicad_sch
* src_file_repo_kicad_sch_link: https://github.com/gregdavill/advent-calendar-of-circuits-2020/tree/main/led-panel/kicad-src/led-panel.kicad_sch

* src_file_repo_sch: 
* src_file_repo_sch_link: https://github.com/gregdavill/advent-calendar-of-circuits-2020/tree/main/
* full details link: https://github.com/oomlout/oomlout_oomp_project_bot_v_2/tree/main/projects/gregdavill_advent_calendar_of_circuits_2020_led_panel/current_version/working

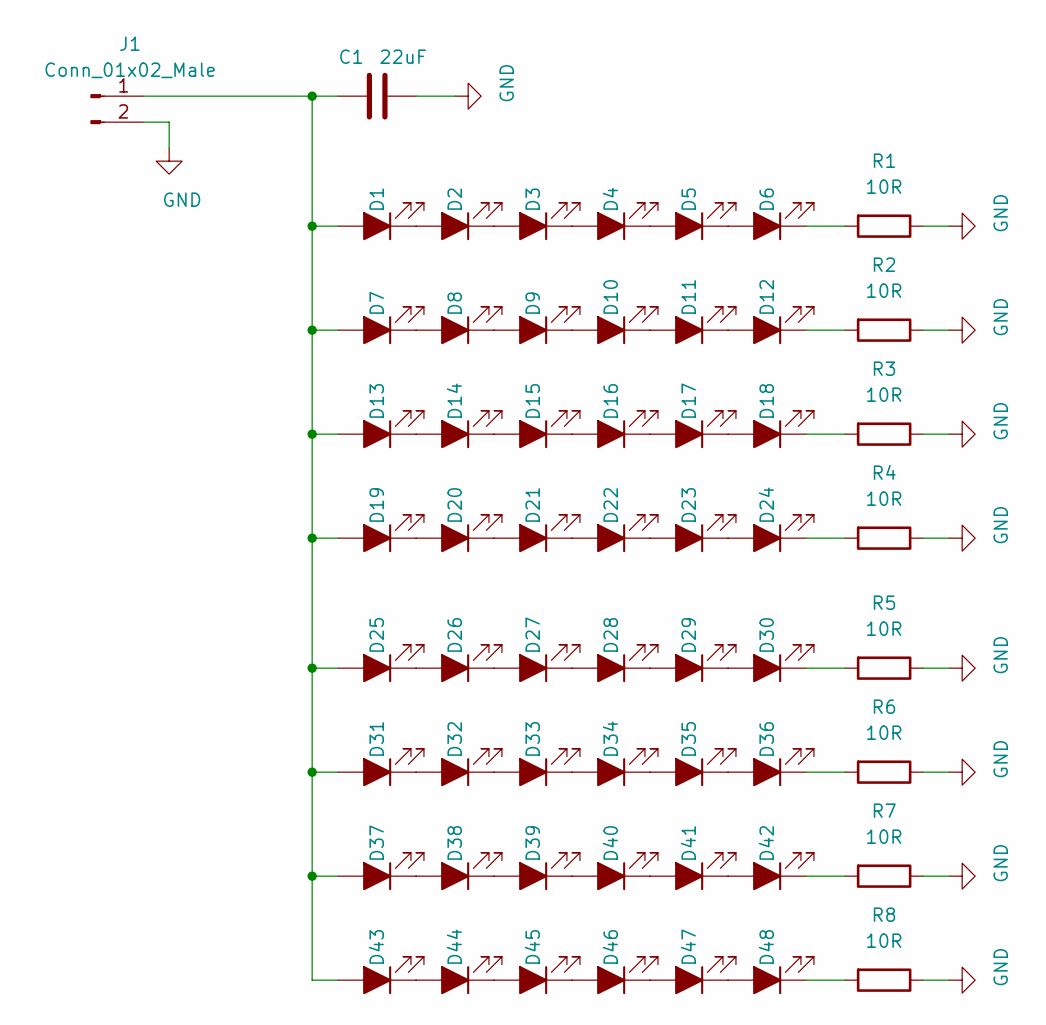
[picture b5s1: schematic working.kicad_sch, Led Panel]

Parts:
C1: 22uF; C_1210_3225Metric
D1, D2, D3, D4, D5, D6, D7, D8, D9, D10, D11, D12, D13, D14, D15, D16, D17, D18, D19, D20, D21, D22, D23, D24, D25, D26, D27, D28, D29, D30, D31, D32, D33, D34, D35, D36, D37, D38, D39, D40, D41, D42, D43, D44, D45, D46, D47, D48: LED_ALT; LED_LUXEON_3014
J1: Conn_01x02_Male; PinHeader_1x02_P2.54mm_Horizontal
R1, R2, R3, R4, R5, R6, R7, R8: 10R; R_0603_1608Metric

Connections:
GND: C1.2, J1.2, R1.1, R2.1, R3.1, R4.1, R5.1, R6.1, R7.1, R8.1
unnamed: C1.1, D1.2 (A), D7.2 (A), D13.2 (A), D19.2 (A), D25.2 (A), D31.2 (A), D37.2 (A), D43.2 (A), J1.1
unnamed: D1.1 (K), D2.2 (A)
unnamed: D2.1 (K), D3.2 (A)
unnamed: D3.1 (K), D4.2 (A)
unnamed: D4.1 (K), D5.2 (A)
unnamed: D5.1 (K), D6.2 (A)
unnamed: D6.1 (K), R1.2
unnamed: D7.1 (K), D8.2 (A)
unnamed: D8.1 (K), D9.2 (A)
unnamed: D10.1 (K), D11.2 (A)
unnamed: D9.1 (K), D10.2 (A)
unnamed: D11.1 (K), D12.2 (A)
unnamed: D12.1 (K), R2.2
unnamed: D13.1 (K), D14.2 (A)
unnamed: D14.1 (K), D15.2 (A)
unnamed: D15.1 (K), D16.2 (A)
unnamed: D16.1 (K), D17.2 (A)
unnamed: D17.1 (K), D18.2 (A)
unnamed: D18.1 (K), R3.2
unnamed: D19.1 (K), D20.2 (A)
unnamed: D20.1 (K), D21.2 (A)
unnamed: D21.1 (K), D22.2 (A)
unnamed: D22.1 (K), D23.2 (A)
unnamed: D23.1 (K), D24.2 (A)
unnamed: D24.1 (K), R4.2
unnamed: D25.1 (K), D26.2 (A)
unnamed: D26.1 (K), D27.2 (A)
unnamed: D27.1 (K), D28.2 (A)
unnamed: D28.1 (K), D29.2 (A)
unnamed: D29.1 (K), D30.2 (A)
unnamed: D30.1 (K), R5.2
unnamed: D31.1 (K), D32.2 (A)
unnamed: D32.1 (K), D33.2 (A)
unnamed: D33.1 (K), D34.2 (A)
unnamed: D34.1 (K), D35.2 (A)
unnamed: D35.1 (K), D36.2 (A)
unnamed: D36.1 (K), R6.2
unnamed: D37.1 (K), D38.2 (A)
unnamed: D38.1 (K), D39.2 (A)
unnamed: D39.1 (K), D40.2 (A)
unnamed: D40.1 (K), D41.2 (A)
unnamed: D41.1 (K), D42.2 (A)
unnamed: D42.1 (K), R7.2
unnamed: D43.1 (K), D44.2 (A)
unnamed: D44.1 (K), D45.2 (A)
unnamed: D45.1 (K), D46.2 (A)
unnamed: D46.1 (K), D47.2 (A)
unnamed: D47.1 (K), D48.2 (A)
unnamed: D48.1 (K), R8.2

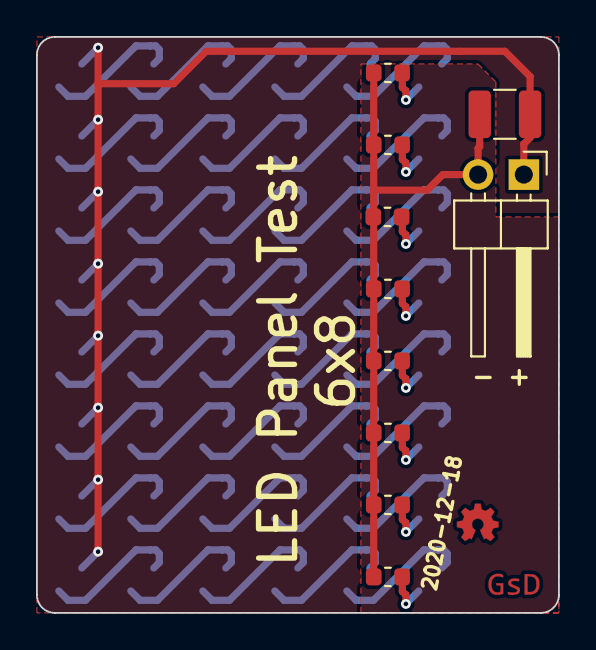
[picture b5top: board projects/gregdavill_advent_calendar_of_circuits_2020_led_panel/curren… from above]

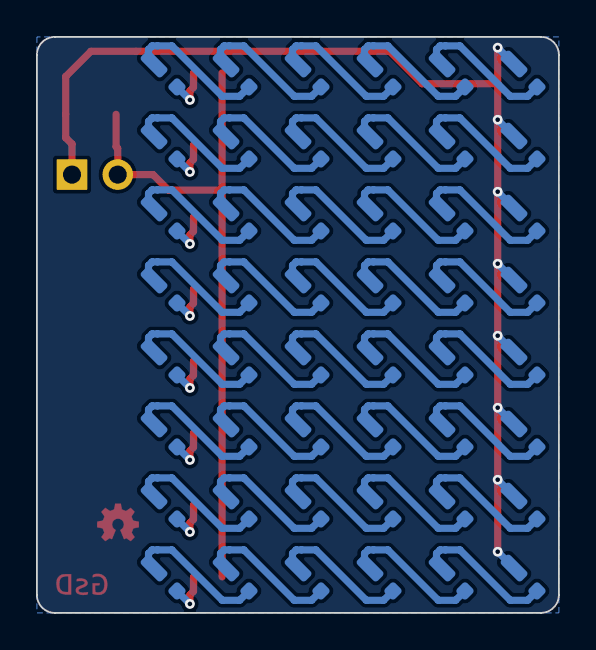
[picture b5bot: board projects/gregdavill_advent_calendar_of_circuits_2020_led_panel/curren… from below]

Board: 2 copper layers, 29.0 x 32.0 mm, 58 parts (48 on the bottom side), 50 nets.

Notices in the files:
projects/gregdavill_advent_calendar_of_circuits_2020_icebreaker_/current_version/working/working.kicad_pcb:
License: CC-BY-SA 4.0
GsD (C) 2020
CC-BY-SA 4.0
(C) 2020
